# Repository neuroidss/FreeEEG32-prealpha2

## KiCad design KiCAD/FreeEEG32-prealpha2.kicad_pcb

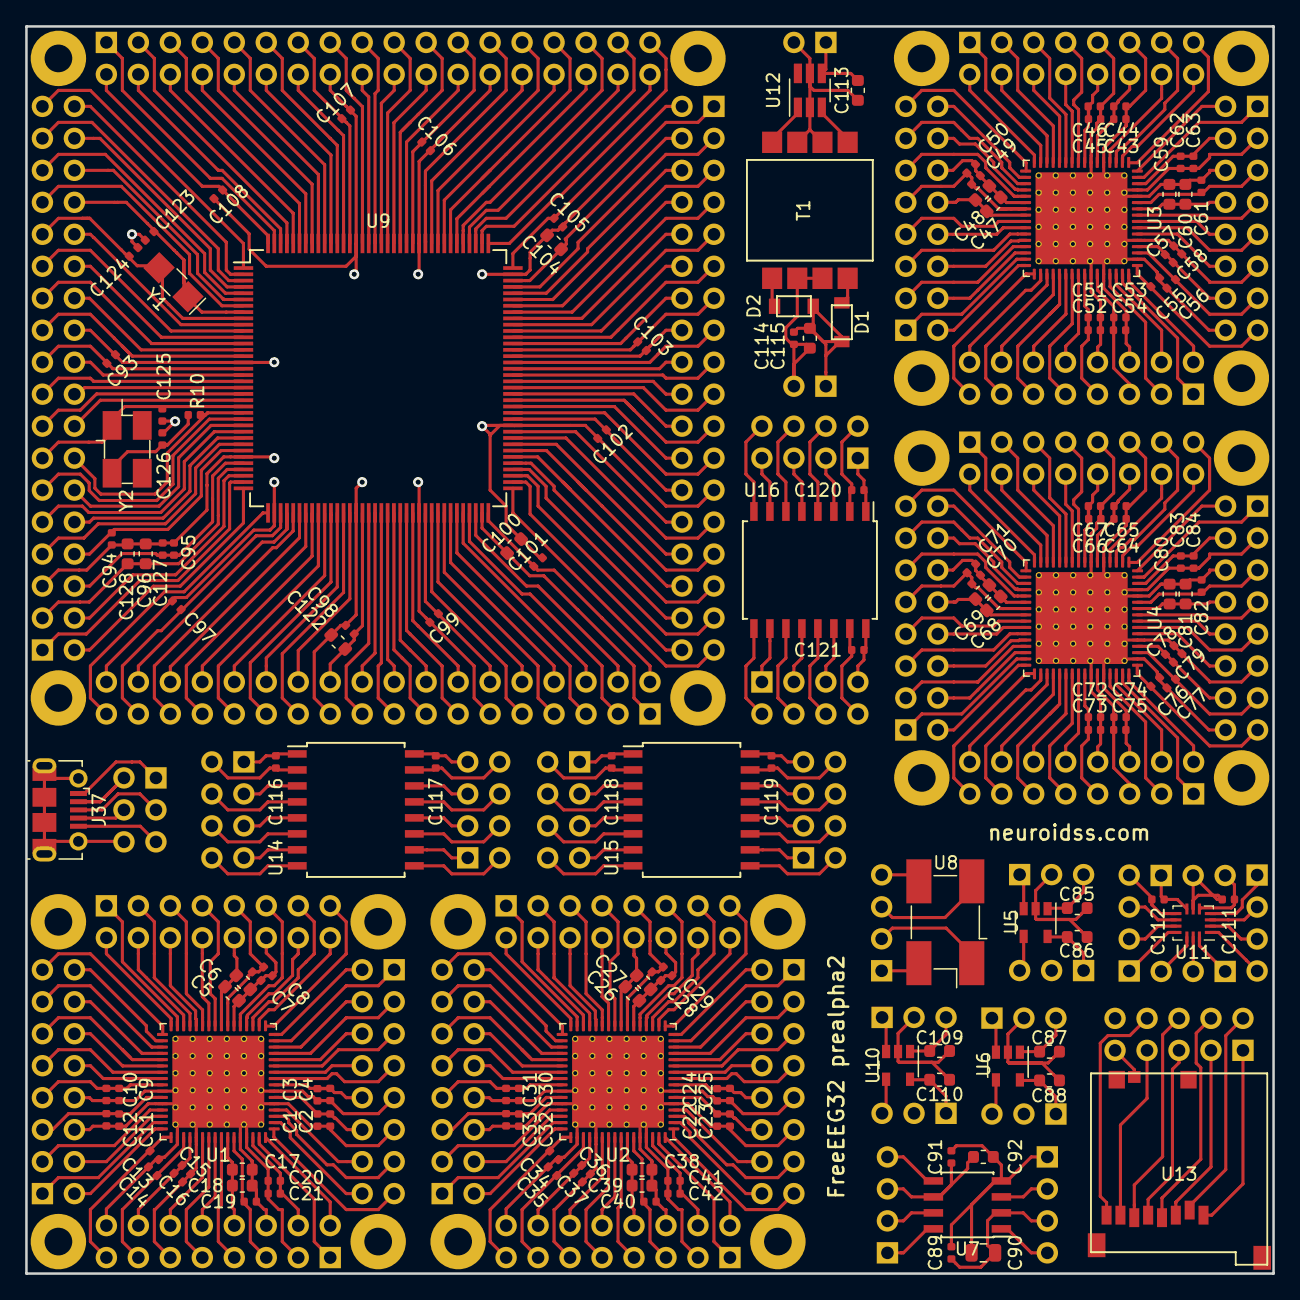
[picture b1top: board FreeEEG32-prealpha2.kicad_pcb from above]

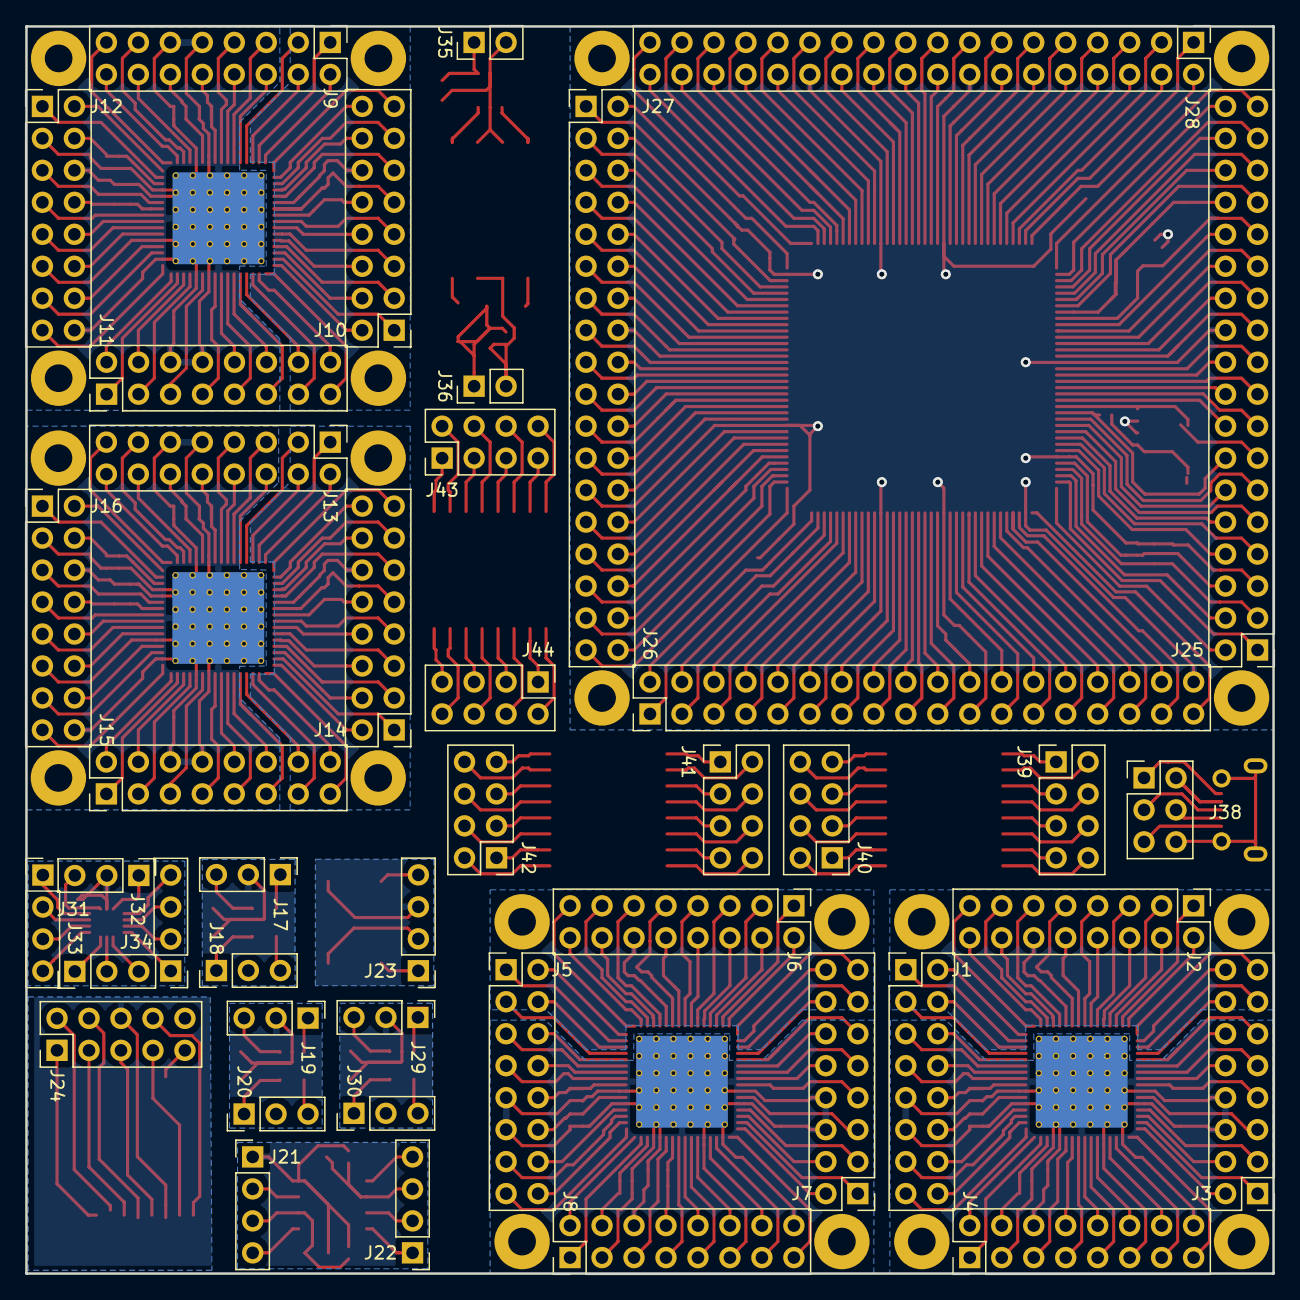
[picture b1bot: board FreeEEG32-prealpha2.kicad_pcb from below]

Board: 2 copper layers, 99.1 x 99.1 mm, 194 parts (43 on the bottom side), 476 nets.

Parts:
C1, C3, C7, C9, C11, C13, C14, C15, C19, C20, C22, C24, C28, C30, C32, C34, C35, C36, C40, C41, C43, C45, C49, C51, C53, C55, C56, C57, C61, C62, C64, C66, C70, C72, C74, C76, C77, C78, C82, C83, C89, C91, C93, C94, C95, C97, C98, C99, C101, C102, C103, C105, C106, C107, C108, C111, C112, C114, C116, C117, C118, C119, C120, C121: 100n; C_0402_1005Metric
C2, C4, C8, C10, C12, C16, C21, C23, C25, C29, C31, C33, C37, C42, C44, C46, C50, C52, C54, C58, C63, C65, C67, C71, C73, C75, C79, C84, C127: 1u; C_0402_1005Metric
C5, C17, C26, C38, C47, C59, C68, C80, C96: 100n; C_0603_1608Metric
C6, C18, C27, C39, C48, C60, C69, C81, C128: 1u; C_0603_1608Metric
C85, C86, C87, C88, C100, C104, C109, C110: 2.2u; C_0603_1608Metric
C90: 22u; C_0805_2012Metric
C92, C113, C115: 10u; C_0603_1608Metric
C122: 4.7u; C_0603_1608Metric
C123, C125: CL1; C_0402_1005Metric
C124, C126: CL2; C_0402_1005Metric
D1, D2: D_Schottky; SOD−123
J1, J2, J3, J4, J5, J6, J7, J8, J9, J10, J11, J12, J13, J14, J15, J16: Conn_02x08_Odd_Even; PinHeader_2x08_P2.54mm_Vertical
J17, J18, J19, J20, J29, J30, J32, J33: Conn_01x03; PinHeader_1x03_P2.54mm_Vertical
J21, J22, J23, J31, J34: Conn_01x04; PinHeader_1x04_P2.54mm_Vertical
J24: Conn_02x05_Odd_Even; PinHeader_2x05_P2.54mm_Vertical
J25, J26, J27, J28: Conn_02x18_Odd_Even; PinHeader_2x18_P2.54mm_Vertical
J35, J36: Conn_01x02; PinHeader_1x02_P2.54mm_Vertical
J37: USB_B_Micro; USB_Micro-B_Molex-105017-0001
J38: Conn_02x03_Odd_Even; PinHeader_2x03_P2.54mm_Vertical
J39, J40, J41, J42, J43, J44: Conn_02x04_Odd_Even; PinHeader_2x04_P2.54mm_Vertical
R10: R_EXT; R_0402_1005Metric
T1: da2303; SMT Power Transformer
U1, U2, U3, U4: AD7779; QFN-64-1EP_9x9mm_P0.5mm_EP7.3x7.3mm_ThermalVias
U5, U6, U10: LP5907; SOT-23-5
U7: ADR4525; SOIC-8_3.9x4.9mm_P1.27mm
U8: FXO-SM7_OSC-SMD7050_short; Oscillator_SMD_EuroQuartz_XO91-4Pin_7.0x5.0mm_HandSoldering
U9: STM32F765ZITx; LQFP-144_20x20mm_P0.5mm
U11: LSM6DS3; Bosch_LGA-14_3x2.5mm_P0.5mm
U12: SN6505A; SOT-23-6_Handsoldering
U13: 473521001
U14, U15, U16: ISO7341c; SOIC-16W_7.5x10.3mm_P1.27mm
Y1: 32768Hz; Crystal_SMD_EuroQuartz_EQ161-2Pin_3.2x1.5mm_HandSoldering
Y2: 8MHz; Crystal_SMD_EuroQuartz_MJ-4Pin_5.0x3.2mm_HandSoldering

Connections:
/ACCEL&GYRO/1_SDO/SA0: J31.4, U11.1
/ACCEL&GYRO/2_SDx: J31.3, U11.2
/ACCEL&GYRO/3_SCx: J31.2, U11.3
/ACCEL&GYRO/4_INT1: J31.1, U11.4
/ACCEL&GYRO/5_VDDIO: C111.1, J32.3, U11.5
/ACCEL&GYRO/6_GND: C111.2, J32.2, U11.6
/ACCEL&GYRO/7_GND: C112.2, J32.1, U11.7
/ACCEL&GYRO/8_VDD: C112.1, J34.4, U11.8
/ACCEL&GYRO/9_INT2: J34.3, U11.9
/ACCEL&GYRO/10_NC: J34.2, U11.10
/ACCEL&GYRO/11_NC: J34.1, U11.11
/ACCEL&GYRO/12_CS: J33.3, U11.12
/ACCEL&GYRO/13_SCL: J33.2, U11.13
/ACCEL&GYRO/14_SDA: J33.1, U11.14
/ADC1/1_AIN0-: J1.15, U1.1
/ADC1/2_AIN0+: J1.16, U1.2
/ADC1/3_AIN1-: J1.13, U1.3
/ADC1/4_AIN1+: J1.14, U1.4
/ADC1/9_AIN2-: J1.7, U1.9
/ADC1/10_AIN2+: J1.8, U1.10
/ADC1/11_AIN3-: J1.5, U1.11
/ADC1/12_AIN3+: J1.6, U1.12
/ADC1/13_MODE0_GPIO0: J1.3, U1.13
/ADC1/14_MODE1_GPIO1: J1.4, U1.14
/ADC1/15_MODE2_GPIO2: J1.1, U1.15
/ADC1/16_MODE3_ALERT: J1.2, U1.16
/ADC1/37_AIN7+: J3.11, U1.37
/ADC1/38_AIN7-: J3.12, U1.38
/ADC1/39_AIN6+: J3.9, U1.39
/ADC1/40_AIN6-: J3.10, U1.40
/ADC1/45_AIN5+: J3.3, U1.45
/ADC1/46_AIN5-: J3.4, U1.46
/ADC1/47_AIN4+: J3.1, U1.47
/ADC1/48_AIN4-: J3.2, U1.48
/ADC1/49_REF_OUT: C13.1, J4.15, U1.49
/ADC1/51_AREG2CAP: C14.1, J4.13, U1.51
/ADC1/57_VCM: J4.7, U1.57
/ADC1/59_AREG1CAP: C19.1, J4.5, U1.59
/ADC1/63_AUXAIN+: J4.1, U1.63
/ADC1/64_AUXAIN-: J4.2, U1.64
/ADC1_6_AVDD1A: C1.2, C2.2, J1.12, U1.6
/ADC1_8_REF1+: C3.2, C4.2, J1.10, U1.8
/ADC1_17_CONVST_SAR: J2.15, U1.17
/ADC1_18_ALERT_CS: J2.16, U1.18
/ADC1_19_DCLK2_SCLK: J2.13, U1.19
/ADC1_20_DCLK1_SDI: J2.14, U1.20
/ADC1_21_DCLK0_SDO: J2.11, U1.21
/ADC1_22_DGND: C5.1, C6.1, C7.1, C8.1, J2.12, U1.22
/ADC1_23_DREGCAP: C7.2, C8.2, J2.9, U1.23
/ADC1_24_IOVDD: C5.2, C6.2, J2.10, U1.24
/ADC1_25_DOUT3: J2.7, U1.25
/ADC1_26_DOUT2: J2.8, U1.26
/ADC1_27_DOUT1: J2.5, U1.27
/ADC1_28_DOUT0: J2.6, U1.28
/ADC1_29_DCLK: J2.3, U1.29
/ADC1_30_DRDY: J2.4, U1.30
/ADC1_31_XTAL1: J2.1, U1.31
/ADC1_32_XTAL2_MCLK: J2.2, U1.32
/ADC1_33_START: J3.15, U1.33
/ADC1_34_SYNC_OUT: J3.16, U1.34
/ADC1_35_SYNC_IN: J3.13, U1.35
/ADC1_36_RESET: J3.14, U1.36
/ADC1_41_REF2+: C9.2, C10.2, J3.7, U1.41
/ADC1_42_REF2-: C1.1, C2.1, C3.1, C4.1, C9.1, C10.1, C11.1, C12.1, C13.2, C14.2, C15.1, C16.1, C17.1, C18.1, C19.2, C20.2, C21.2, J1.9, J1.11, J3.6, J3.8, J4.3, J4.6, J4.11, J4.16, U1.5, U1.7, U1.42, U1.44, U1.50, U1.53, U1.60, U1.61, U1.65
/ADC1_43_AVDD1B: C11.2, C12.2, J3.5, U1.43
/ADC1_52_AVDD2B: C15.2, C16.2, J4.14, U1.52
/ADC1_54_FORMAT1: J4.12, U1.54
/ADC1_55_FORMAT0: J4.9, U1.55
/ADC1_56_CLK_SEL: J4.10, U1.56
/ADC1_58_AVDD2A: C17.2, C18.2, J4.8, U1.58
/ADC1_62_AVDD4: C20.1, C21.1, J4.4, U1.62
/ADC2/1_AIN0-: J5.15, U2.1
/ADC2/2_AIN0+: J5.16, U2.2
/ADC2/3_AIN1-: J5.13, U2.3
/ADC2/4_AIN1+: J5.14, U2.4
/ADC2/9_AIN2-: J5.7, U2.9
/ADC2/10_AIN2+: J5.8, U2.10
/ADC2/11_AIN3-: J5.5, U2.11
/ADC2/12_AIN3+: J5.6, U2.12
/ADC2/13_MODE0_GPIO0: J5.3, U2.13
/ADC2/14_MODE1_GPIO1: J5.4, U2.14
/ADC2/15_MODE2_GPIO2: J5.1, U2.15
/ADC2/16_MODE3_ALERT: J5.2, U2.16
/ADC2/37_AIN7+: J7.11, U2.37
/ADC2/38_AIN7-: J7.12, U2.38
/ADC2/39_AIN6+: J7.9, U2.39
/ADC2/40_AIN6-: J7.10, U2.40
/ADC2/45_AIN5+: J7.3, U2.45
/ADC2/46_AIN5-: J7.4, U2.46
/ADC2/47_AIN4+: J7.1, U2.47
/ADC2/48_AIN4-: J7.2, U2.48
/ADC2/49_REF_OUT: C34.1, J8.15, U2.49
/ADC2/51_AREG2CAP: C35.1, J8.13, U2.51
/ADC2/57_VCM: J8.7, U2.57
/ADC2/59_AREG1CAP: C40.1, J8.5, U2.59
/ADC2/63_AUXAIN+: J8.1, U2.63
/ADC2/64_AUXAIN-: J8.2, U2.64
/ADC2_6_AVDD1A: C22.2, C23.2, J5.12, U2.6
/ADC2_8_REF1+: C24.2, C25.2, J5.10, U2.8
/ADC2_17_CONVST_SAR: J6.15, U2.17
/ADC2_18_ALERT_CS: J6.16, U2.18
/ADC2_19_DCLK2_SCLK: J6.13, U2.19
/ADC2_20_DCLK1_SDI: J6.14, U2.20
/ADC2_21_DCLK0_SDO: J6.11, U2.21
/ADC2_22_DGND: C26.1, C27.1, C28.1, C29.1, J6.12, U2.22
/ADC2_23_DREGCAP: C28.2, C29.2, J6.9, U2.23
/ADC2_24_IOVDD: C26.2, C27.2, J6.10, U2.24
/ADC2_25_DOUT3: J6.7, U2.25
/ADC2_26_DOUT2: J6.8, U2.26
/ADC2_27_DOUT1: J6.5, U2.27
/ADC2_28_DOUT0: J6.6, U2.28
/ADC2_29_DCLK: J6.3, U2.29
/ADC2_30_DRDY: J6.4, U2.30
/ADC2_31_XTAL1: J6.1, U2.31
/ADC2_32_XTAL2_MCLK: J6.2, U2.32
/ADC2_33_START: J7.15, U2.33
/ADC2_34_SYNC_OUT: J7.16, U2.34
/ADC2_35_SYNC_IN: J7.13, U2.35
/ADC2_36_RESET: J7.14, U2.36
/ADC2_41_REF2+: C30.2, C31.2, J7.7, U2.41
/ADC2_42_REF2-: C22.1, C23.1, C24.1, C25.1, C30.1, C31.1, C32.1, C33.1, C34.2, C35.2, C36.1, C37.1, C38.1, C39.1, C40.2, C41.2, C42.2, J5.9, J5.11, J7.6, J7.8, J8.3, J8.6, J8.11, J8.16, U2.5, U2.7, U2.42, U2.44, U2.50, U2.53, U2.60, U2.61, U2.65
/ADC2_43_AVDD1B: C32.2, C33.2, J7.5, U2.43
/ADC2_52_AVDD2B: C36.2, C37.2, J8.14, U2.52
/ADC2_54_FORMAT1: J8.12, U2.54
/ADC2_55_FORMAT0: J8.9, U2.55
/ADC2_56_CLK_SEL: J8.10, U2.56
/ADC2_58_AVDD2A: C38.2, C39.2, J8.8, U2.58
/ADC2_62_AVDD4: C41.1, C42.1, J8.4, U2.62
/ADC3/1_AIN0-: J9.15, U3.1
/ADC3/2_AIN0+: J9.16, U3.2
/ADC3/3_AIN1-: J9.13, U3.3
/ADC3/4_AIN1+: J9.14, U3.4
/ADC3/9_AIN2-: J9.7, U3.9
/ADC3/10_AIN2+: J9.8, U3.10
/ADC3/11_AIN3-: J9.5, U3.11
/ADC3/12_AIN3+: J9.6, U3.12
/ADC3/13_MODE0_GPIO0: J9.3, U3.13
/ADC3/14_MODE1_GPIO1: J9.4, U3.14
/ADC3/15_MODE2_GPIO2: J9.1, U3.15
/ADC3/16_MODE3_ALERT: J9.2, U3.16
/ADC3/37_AIN7+: J11.11, U3.37
/ADC3/38_AIN7-: J11.12, U3.38
/ADC3/39_AIN6+: J11.9, U3.39
/ADC3/40_AIN6-: J11.10, U3.40
/ADC3/45_AIN5+: J11.3, U3.45
/ADC3/46_AIN5-: J11.4, U3.46
/ADC3/47_AIN4+: J11.1, U3.47
/ADC3/48_AIN4-: J11.2, U3.48
/ADC3/49_REF_OUT: C55.1, J12.15, U3.49
/ADC3/51_AREG2CAP: C56.1, J12.13, U3.51
/ADC3/57_VCM: J12.7, U3.57
/ADC3/59_AREG1CAP: C61.1, J12.5, U3.59
/ADC3/63_AUXAIN+: J12.1, U3.63
/ADC3/64_AUXAIN-: J12.2, U3.64
/ADC3_6_AVDD1A: C43.2, C44.2, J9.12, U3.6
/ADC3_8_REF1+: C45.2, C46.2, J9.10, U3.8
/ADC3_17_CONVST_SAR: J10.15, U3.17
/ADC3_18_ALERT_CS: J10.16, U3.18
/ADC3_19_DCLK2_SCLK: J10.13, U3.19
/ADC3_20_DCLK1_SDI: J10.14, U3.20
/ADC3_21_DCLK0_SDO: J10.11, U3.21
/ADC3_22_DGND: C47.1, C48.1, C49.1, C50.1, J10.12, U3.22
/ADC3_23_DREGCAP: C49.2, C50.2, J10.9, U3.23
/ADC3_24_IOVDD: C47.2, C48.2, J10.10, U3.24
/ADC3_25_DOUT3: J10.7, U3.25
/ADC3_26_DOUT2: J10.8, U3.26
/ADC3_27_DOUT1: J10.5, U3.27
/ADC3_28_DOUT0: J10.6, U3.28
/ADC3_29_DCLK: J10.3, U3.29
/ADC3_30_DRDY: J10.4, U3.30
/ADC3_31_XTAL1: J10.1, U3.31
/ADC3_32_XTAL2_MCLK: J10.2, U3.32
/ADC3_33_START: J11.15, U3.33
/ADC3_34_SYNC_OUT: J11.16, U3.34
/ADC3_35_SYNC_IN: J11.13, U3.35
/ADC3_36_RESET: J11.14, U3.36
/ADC3_41_REF2+: C51.2, C52.2, J11.7, U3.41
/ADC3_42_REF2-: C43.1, C44.1, C45.1, C46.1, C51.1, C52.1, C53.1, C54.1, C55.2, C56.2, C57.1, C58.1, C59.1, C60.1, C61.2, C62.2, C63.2, J9.9, J9.11, J11.6, J11.8, J12.3, J12.6, J12.11, J12.16, U3.5, U3.7, U3.42, U3.44, U3.50, U3.53, U3.60, U3.61, U3.65
/ADC3_43_AVDD1B: C53.2, C54.2, J11.5, U3.43
/ADC3_52_AVDD2B: C57.2, C58.2, J12.14, U3.52
/ADC3_54_FORMAT1: J12.12, U3.54
/ADC3_55_FORMAT0: J12.9, U3.55
/ADC3_56_CLK_SEL: J12.10, U3.56
/ADC3_58_AVDD2A: C59.2, C60.2, J12.8, U3.58
/ADC3_62_AVDD4: C62.1, C63.1, J12.4, U3.62
/ADC4/1_AIN0-: J13.15, U4.1
/ADC4/2_AIN0+: J13.16, U4.2
/ADC4/3_AIN1-: J13.13, U4.3
/ADC4/4_AIN1+: J13.14, U4.4
/ADC4/9_AIN2-: J13.7, U4.9
/ADC4/10_AIN2+: J13.8, U4.10
/ADC4/11_AIN3-: J13.5, U4.11
/ADC4/12_AIN3+: J13.6, U4.12
/ADC4/13_MODE0_GPIO0: J13.3, U4.13
/ADC4/14_MODE1_GPIO1: J13.4, U4.14
/ADC4/15_MODE2_GPIO2: J13.1, U4.15
/ADC4/16_MODE3_ALERT: J13.2, U4.16
/ADC4/37_AIN7+: J15.11, U4.37
/ADC4/38_AIN7-: J15.12, U4.38
/ADC4/39_AIN6+: J15.9, U4.39
/ADC4/40_AIN6-: J15.10, U4.40
/ADC4/45_AIN5+: J15.3, U4.45
/ADC4/46_AIN5-: J15.4, U4.46
/ADC4/47_AIN4+: J15.1, U4.47
/ADC4/48_AIN4-: J15.2, U4.48
/ADC4/49_REF_OUT: C76.1, J16.15, U4.49
/ADC4/51_AREG2CAP: C77.1, J16.13, U4.51
/ADC4/57_VCM: J16.7, U4.57
/ADC4/59_AREG1CAP: C82.1, J16.5, U4.59
/ADC4/63_AUXAIN+: J16.1, U4.63
/ADC4/64_AUXAIN-: J16.2, U4.64
/ADC4_6_AVDD1A: C64.2, C65.2, J13.12, U4.6
/ADC4_8_REF1+: C66.2, C67.2, J13.10, U4.8
/ADC4_17_CONVST_SAR: J14.15, U4.17
/ADC4_18_ALERT_CS: J14.16, U4.18
/ADC4_19_DCLK2_SCLK: J14.13, U4.19
/ADC4_20_DCLK1_SDI: J14.14, U4.20
/ADC4_21_DCLK0_SDO: J14.11, U4.21
/ADC4_22_DGND: C68.1, C69.1, C70.1, C71.1, J14.12, U4.22
/ADC4_23_DREGCAP: C70.2, C71.2, J14.9, U4.23
/ADC4_24_IOVDD: C68.2, C69.2, J14.10, U4.24
/ADC4_25_DOUT3: J14.7, U4.25
/ADC4_26_DOUT2: J14.8, U4.26
/ADC4_27_DOUT1: J14.5, U4.27
/ADC4_28_DOUT0: J14.6, U4.28
/ADC4_29_DCLK: J14.3, U4.29
/ADC4_30_DRDY: J14.4, U4.30
/ADC4_31_XTAL1: J14.1, U4.31
/ADC4_32_XTAL2_MCLK: J14.2, U4.32
/ADC4_33_START: J15.15, U4.33
/ADC4_34_SYNC_OUT: J15.16, U4.34
/ADC4_35_SYNC_IN: J15.13, U4.35
/ADC4_36_RESET: J15.14, U4.36
/ADC4_41_REF2+: C72.2, C73.2, J15.7, U4.41
/ADC4_42_REF2-: C64.1, C65.1, C66.1, C67.1, C72.1, C73.1, C74.1, C75.1, C76.2, C77.2, C78.1, C79.1, C80.1, C81.1, C82.2, C83.2, C84.2, J13.9, J13.11, J15.6, J15.8, J16.3, J16.6, J16.11, J16.16, U4.5, U4.7, U4.42, U4.44, U4.50, U4.53, U4.60, U4.61, U4.65
/ADC4_43_AVDD1B: C74.2, C75.2, J15.5, U4.43
/ADC4_52_AVDD2B: C78.2, C79.2, J16.14, U4.52
/ADC4_54_FORMAT1: J16.12, U4.54
/ADC4_55_FORMAT0: J16.9, U4.55
/ADC4_56_CLK_SEL: J16.10, U4.56
/ADC4_58_AVDD2A: C80.2, C81.2, J16.8, U4.58
/ADC4_62_AVDD4: C83.1, C84.1, J16.4, U4.62
/AVDD/4_NC: J18.3, U5.4
/AVDD_1_IN: C85.1, J17.3, U5.1
/AVDD_2_GND: C85.2, C86.2, J17.2, U5.2
/AVDD_3_EN: J17.1, U5.3
/AVDD_5_OUT: C86.1, J18.1, U5.5
/CRYSTAL/1_NC: J23.2, U8.1
/CRYSTAL_2_GND: J23.3, U8.2
/CRYSTAL_3_OUT: J23.4, U8.3
/CRYSTAL_4_Vin: J23.1, U8.4
/IOVDD/4_NC: J20.3, U6.4
/IOVDD_1_IN: C87.1, J19.3, U6.1
/IOVDD_2_GND: C87.2, C88.2, J19.2, U6.2
/IOVDD_3_EN: J19.1, U6.3
/IOVDD_5_OUT: C88.1, J20.1, U6.5
/ISO1/1_VCC1: C116.1, J39.1, U14.1
/ISO1/2_GND1: C116.2, J39.2, U14.2
/ISO1/3_INA: J39.3, U14.3
/ISO1/4_INB: J39.4, U14.4
/ISO1/5_INC: J39.5, U14.5
/ISO1/6_OUTD: J39.6, U14.6
/ISO1/7_EN1: J39.7, U14.7
/ISO1/8_GND1: J39.8, U14.8
/ISO1/9_GND2: J40.2, U14.9
/ISO1/10_EN2: J40.1, U14.10
/ISO1/11_IND: J40.4, U14.11
/ISO1/12_OUTC: J40.3, U14.12
/ISO1/13_OUTB: J40.6, U14.13
/ISO1/14_OUTA: J40.5, U14.14
/ISO1/15_GND2: C117.2, J40.8, U14.15
/ISO1/16_VCC2: C117.1, J40.7, U14.16
/ISO2/1_VCC1: C118.1, J41.1, U15.1
/ISO2/2_GND1: C118.2, J41.2, U15.2
/ISO2/3_INA: J41.3, U15.3
/ISO2/4_INB: J41.4, U15.4
/ISO2/5_INC: J41.5, U15.5
/ISO2/6_OUTD: J41.6, U15.6
/ISO2/7_EN1: J41.7, U15.7
/ISO2/8_GND1: J41.8, U15.8
/ISO2/9_GND2: J42.2, U15.9
/ISO2/10_EN2: J42.1, U15.10
/ISO2/11_IND: J42.4, U15.11
/ISO2/12_OUTC: J42.3, U15.12
/ISO2/13_OUTB: J42.6, U15.13
/ISO2/14_OUTA: J42.5, U15.14
/ISO2/15_GND2: C119.2, J42.8, U15.15
/ISO2/16_VCC2: C119.1, J42.7, U15.16
/ISO3/1_VCC1: C120.1, J43.1, U16.1
/ISO3/2_GND1: C120.2, J43.2, U16.2
/ISO3/3_INA: J43.3, U16.3
/ISO3/4_INB: J43.4, U16.4
/ISO3/5_INC: J43.5, U16.5
/ISO3/6_OUTD: J43.6, U16.6
/ISO3/7_EN1: J43.7, U16.7
/ISO3/8_GND1: J43.8, U16.8
/ISO3/9_GND2: J44.2, U16.9
/ISO3/10_EN2: J44.1, U16.10
/ISO3/11_IND: J44.4, U16.11
/ISO3/12_OUTC: J44.3, U16.12
/ISO3/13_OUTB: J44.6, U16.13
/ISO3/14_OUTA: J44.5, U16.14
/ISO3/15_GND2: C121.2, J44.8, U16.15
/ISO3/16_VCC2: C121.1, J44.7, U16.16
/MCU/1_PE2: J25.35, U9.1
/MCU/2_PE3: J25.36, U9.2
/MCU/3_PE4: J25.33, U9.3
/MCU/4_PE5: J25.34, U9.4
/MCU/5_PE6: J25.31, U9.5
/MCU/6_VBAT: J25.32, U9.6
/MCU/7_PC13: J25.29, U9.7
/MCU/8_PC14: C123.1, J25.30, U9.8, Y1.1
/MCU/9_PC15: C124.1, J25.27, U9.9, Y1.2
/MCU/10_PF0: J25.28, U9.10
/MCU/11_PF1: J25.25, U9.11
/MCU/12_PF2: J25.26, U9.12
/MCU/13_PF3: J25.23, U9.13
/MCU/14_PF4: J25.24, U9.14
/MCU/15_PF5: J25.21, U9.15
/MCU/18_PF6: J25.20, U9.18
/MCU/19_PF7: J25.17, U9.19
/MCU/20_PF8: J25.18, U9.20
/MCU/21_PF9: J25.15, U9.21
/MCU/22_PF10: J25.16, U9.22
/MCU/23_PH0: C125.1, J25.13, U9.23, Y2.1
/MCU/24_PH1: J25.14, R10.1, U9.24
/MCU/25_NRST: J25.11, U9.25
/MCU/26_PC0: J25.12, U9.26
/MCU/27_PC1: J25.9, U9.27
/MCU/28_PC2: J25.10, U9.28
/MCU/29_PC3: J25.7, U9.29
/MCU/32_VREF+: C95.1, C127.1, J25.6, U9.32
/MCU/34_PA0: J25.4, U9.34
/MCU/35_PA1: J25.1, U9.35
/MCU/36_PA2: J25.2, U9.36
/MCU/37_PA3: J26.35, U9.37
/MCU/40_PA4: J26.34, U9.40
/MCU/41_PA5: J26.31, U9.41
/MCU/42_PA6: J26.32, U9.42
/MCU/43_PA7: J26.29, U9.43
/MCU/44_PC4: J26.30, U9.44
/MCU/45_PC5: J26.27, U9.45
/MCU/46_PB0: J26.28, U9.46
/MCU/47_PB1: J26.25, U9.47
/MCU/48_PB2: J26.26, U9.48
/MCU/49_PF11: J26.23, U9.49
/MCU/50_PF12: J26.24, U9.50
/MCU/53_PF13: J26.19, U9.53
/MCU/54_PF14: J26.20, U9.54
/MCU/55_PF15: J26.17, U9.55
/MCU/56_PG0: J26.18, U9.56
/MCU/57_PG1: J26.15, U9.57
/MCU/58_PE7: J26.16, U9.58
/MCU/59_PE8: J26.13, U9.59
/MCU/60_PE9: J26.14, U9.60
/MCU/63_PE10: J26.9, U9.63
/MCU/64_PE11: J26.10, U9.64
/MCU/65_PE12: J26.7, U9.65
/MCU/66_PE13: J26.8, U9.66
/MCU/67_PE14: J26.5, U9.67
/MCU/68_PE15: J26.6, U9.68
/MCU/69_PB10: J26.3, U9.69
/MCU/70_PB11: J26.4, U9.70
/MCU/71_VCAP_1: C100.1, J26.1, U9.71
/MCU/73_PB12: J27.35, U9.73
/MCU/74_PB13: J27.36, U9.74
/MCU/75_PB14: J27.33, U9.75
/MCU/76_PB15: J27.34, U9.76
/MCU/77_PD8: J27.31, U9.77
/MCU/78_PD9: J27.32, U9.78
/MCU/79_PD10: J27.29, U9.79
/MCU/80_PD11: J27.30, U9.80
/MCU/81_PD12: J27.27, U9.81
/MCU/82_PD13: J27.28, U9.82
/MCU/85_PD14: J27.23, U9.85
/MCU/86_PD15: J27.24, U9.86
/MCU/87_PG2: J27.21, U9.87
/MCU/88_PG3: J27.22, U9.88
/MCU/89_PG4: J27.19, U9.89
/MCU/90_PG5: J27.20, U9.90
/MCU/91_PG6: J27.17, U9.91
/MCU/92_PG7: J27.18, U9.92
/MCU/93_PG8: J27.15, U9.93
/MCU/96_PC6: J27.14, U9.96
/MCU/97_PC7: J27.11, U9.97
/MCU/98_PC8: J27.12, U9.98
/MCU/99_PC9: J27.9, U9.99
/MCU/100_PA8: J27.10, U9.100
/MCU/101_PA9: J27.7, U9.101
/MCU/102_PA10: J27.8, U9.102
/MCU/105_PA13: J27.3, U9.105
/MCU/106_VCAP_2: C104.1, J27.4, U9.106
/MCU/109_PA14: J28.35, U9.109
/MCU/110_PA15: J28.36, U9.110
/MCU/111_PC10: J28.33, U9.111
/MCU/112_PC11: J28.34, U9.112
/MCU/113_PC12: J28.31, U9.113
/MCU/114_PD0: J28.32, U9.114
/MCU/115_PD1: J28.29, U9.115
/MCU/116_PD2: J28.30, U9.116
/MCU/117_PD3: J28.27, U9.117
/MCU/118_PD4: J28.28, U9.118
/MCU/119_PD5: J28.25, U9.119
/MCU/122_PD6: J28.24, U9.122
/MCU/123_PD7: J28.21, U9.123
/MCU/124_PG9: J28.22, U9.124
/MCU/125_PG10: J28.19, U9.125
/MCU/126_PG11: J28.20, U9.126
/MCU/127_PG12: J28.17, U9.127
/MCU/128_PG13: J28.18, U9.128
/MCU/129_PG14: J28.15, U9.129
/MCU/132_PG15: J28.14, U9.132
/MCU/133_PB3: J28.11, U9.133
/MCU/134_PB4: J28.12, U9.134
/MCU/135_PB5: J28.9, U9.135
/MCU/136_PB6: J28.10, U9.136
/MCU/137_PB7: J28.7, U9.137
/MCU/138_BOOT0: J28.8, U9.138
/MCU/139_PB8: J28.5, U9.139
/MCU/140_PB9: J28.6, U9.140
/MCU/141_PE0: J28.3, U9.141
/MCU/142_PE1: J28.4, U9.142
/MCU/143_PDR_ON: J28.1, U9.143
/MCU_17_VDD: C93.1, J25.19, U9.17
/MCU_30_VDD: C94.1, J25.8, U9.30
/MCU_33_VDDA: C96.1, C128.1, J25.3, U9.33
/MCU_39_VDD: C97.1, J26.33, U9.39
/MCU_52_VDD: C98.1, C122.1, J26.22, U9.52
/MCU_62_VDD: C99.1, J26.12, U9.62
/MCU_72_VDD: C101.1, J26.2, U9.72
/MCU_84_VDD: C102.1, J27.26, U9.84
/MCU_95_VDDUSB: C103.1, J27.13, U9.95
/MCU_103_PA11_USB_OTG_FS_DM: J27.5, U9.103
/MCU_104_PA12_USB_OTG_FS_DP: J27.6, U9.104
/MCU_107_VSS: C93.2, C94.2, C95.2, C96.2, C97.2, C98.2, C99.2, C100.2, C101.2, C102.2, C103.2, C104.2, C105.2, C106.2, C107.2, C108.2, C122.2, C123.2, C124.2, C125.2, C126.2, C127.2, C128.2, J25.5, J25.22, J26.11, J26.21, J26.36, J27.1, J27.16, J27.25, J28.16, J28.26, U9.16, U9.31, U9.38, U9.51, U9.61, U9.83, U9.94, U9.107, U9.120, U9.130
/MCU_108_VDD: C105.1, J27.2, U9.108
/MCU_121_VDDSDMMC: C106.1, J28.23, U9.121
/MCU_131_VDD: C107.1, J28.13, U9.131
/MCU_144_VDD: C108.1, J28.2, U9.144
/POWER/1_GND: C113.1, J35.1, U12.4
/POWER/2_VCC: C113.2, J35.2, T1.2, T1.3, U12.2, U12.5
/POWER_3_OUT1A2B_DIODES: C114.1, C115.1, D1.1, D2.1, J36.1
/POWER_4_OUT1B2A: C114.2, C115.2, J36.2, T1.6, T1.7
/REF/1_NC: J21.4, U7.1
/REF/3_NC: J21.2, U7.3
/REF/5_NC: J22.4, U7.5
/REF/7_NC: J22.2, U7.7
/REF/8_TP: J22.1, U7.8
/REF_2_VIN: C89.1, C90.1, J21.3, U7.2
/REF_4_GND: C89.2, C90.2, C91.2, C92.2, J21.1, U7.4
/REF_6_OUT: C91.1, C92.1, J22.3, U7.6
/SD/1_DATA2: J24.1, U13.1
/SD/2_DATA3: J24.2, U13.2
/SD/3_CMD: J24.3, U13.3
/SD/4_VDD: J24.4, U13.4
/SD/5_CLK: J24.5, U13.5
/SD/6_Vss: J24.6, U13.6
/SD/7_DATA0: J24.7, U13.7
/SD/8_DATA1: J24.8, U13.8
/SD/9_DETECT: J24.9, U13.9
/USB/4_ID: J37.4, J38.4
/USB/6_Shield: J37.6, J38.6
/USB_1_VBUS: J37.1, J38.1
/USB_2_D-: J37.2, J38.2
/USB_3_D+: J37.3, J38.3
/USB_5_GND: J37.5, J38.5
/VDD/4_NC: J30.3, U10.4
/VDD_1_IN: C109.1, J29.3, U10.1
/VDD_2_GND: C109.2, C110.2, J29.2, U10.2
/VDD_3_EN: J29.1, U10.3
/VDD_5_OUT: C110.1, J30.1, U10.5
unnamed: C126.1, R10.2, Y2.2
unnamed: D1.2, T1.8
unnamed: D2.2, T1.5
unnamed: T1.1, U12.3
unnamed: T1.4, U12.1

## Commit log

2019-06-06 added usb, crystals
2019-06-06 3d model looks like sd card
2019-06-06 fix lib
